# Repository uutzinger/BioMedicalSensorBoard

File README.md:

# MediBrick

A cost-effective Solution for Biomedical Measurements.

Urs Utzinger, 10/2024 and capstone teams: 24052 (2023/24), 23094 (2022/23).
Biomedical Engineering Department, The University of Arizona.

Table of Content:
<!-- TOC start (generated with https://github.com/derlin/bitdowntoc) -->

- [MediBrick](#medibrick)
   * [Problem Description](#problem-description)
   * [Project Goals](#project-goals)
   * [Measurement Solutions](#measurement-solutions)
   * [Microcontroller and Software](#microcontroller-and-software)
   * [Hardware](#hardware)
      + [Design and Manufacturing ](#design-and-manufacturing)
      + [Enclosures](#enclosures)
   * [Project Status](#project-status)

<!-- TOC end -->

<!-- TOC -->

Posters and Papers: 
- *Open source platform to measure physiological signals in a classroom setting*, BMES 2024 Annual Meeting: Biomedical Engineering Education - Poster Session C, Poster Q15 

## Problem Description

Biomedical engineering students need to practice measuring signals from living systems.
Measurement equipment is needed for classroom laboratories that can safely record common physiological parameters.
For a wide adoption, such equipment should be cost effective and repairable in-house.
Therefore, it should take advantage of existing components that are open source and distributed through domestic channels.
While there are commercial systems available [^fn1] [^fn2], there is no unifying approach that takes advantage of existing third party hardware, gives option to expand functionality at later time and uses open source software.  Such measurement modules could also be readily incorporated into academic research projects.

[^fn1]: Bioradio, https://staging.glneurotech.com/product-category/bioradio-all
[^fn2]: Protocentral https://protocentral.com

**An expandable, low-costs, open-design system is needed that measures physiological parameters in a class room setting in a safe manner.**

## Project Goals
- We strive to create an educational system to measure physiological signals.
- It shall be easily manufactured at an educational institution.
- It shall record, display and store common physiological measurements safely in a class room setting.

## Measurement Solutions
This project consists of the following measurement solutions:

| ECG and Impedance | Electronic Stethoscope and Blood Pressure | Pulse Oximeter | Temperature | Inertial Measurement Unit | Air Quality | Lung Capacity |
| --- | --- | --- | --- | --- | --- | --- |
|  |  |  |  |  |  | N.A. |
|  |  |  |  |  |  | N.A. |

Below are the relevant project files. 

Education Content: &#128214;, Sources used to find a solution: &#10004;, Solution: &#128194;, Assembly Instructions: &#128736;, Software: &#128200;

- **General Physiology Background**
    - [Cardiac Physiology](cardiac_physiology.md) &#128214;
    - [Common Physiologic Measurements](physiologic_measurements.md) &#128214;
- **Electro Cardiogram Solutions**
    - [ECG Measurement](ecg_measurements.md) &#128214;
    - [ECG Solutions](ecg_solutions.md) &#10004;
    - [ECG MediBrick v1](ECG_Board/README.md)
    - [ECG MediBrick v2](Impedance_Potential_Board/README.md) based on MAX30001G &#128194;
        - [Assembly Instructions](Impedance_Potential_Board/assembly.md) &#128736;
- **Bio Impedance Solutions**
    - [Impedance Measurement](impedance_measurements.md) &#128214;
    - [Impedance Solutions](impedance_solutions.md) &#10004;
    - [Impedance MediBrick v1](Impedance_Board/README.md) based on AD5933
    - [Impedance MediBrick v2](Impedance_Potential_Board/README.md) based on MAX30001G &#128194;
        - [Assembly Instructions](Impedance_Potential_Board/assembly.md) &#128736;
- **Stethoscope and Sound**
    - [Sound Measurement](sound_measurement.md)&#128214;
    - [Pressure Measurement](pressure_measurements.md) &#128214;
    - [Sound Solutions](sound_solutions.md) Sound Recording Solutions &#10004;
    - [Pressure Solutions](pressure_solutions.md) Pressure Recording Solutions &#10004;
    - [Stethoscope MediBrick V1](Stethoscope_with_3rdparty_Sound/README.md) PCB Artist I2S codec interfacing with ESP
    - [Stethoscope with Blood Pressure MediBrick V2](Stethoscope_with_Pressure/README.md) &#128194;
        - [Assembly Instructions](Stethoscope_with_Pressure/assembly.md) &#128736;
- **Pulse Oximeter**
    - [SpO<sub>2</sub> Measurement](spo2_measurements.md) &#128214;
    - [SpO<sub>2</sub> Solutions](spo2_solutions.md) &#10004;
    - [SpO<sub>2</sub> MediBrick](SPO2_Board/README.md) &#128194;
        - [Assembly Instructions](SPO2_Board/assembly.md) &#128736;
- **Temperature and Strain Gauges**
    - [Temperature Measurement](temperature_measurements.md) &#128214;
    - [Temperature Solutions](temperature_solutions.md) &#10004;
    - [Temperature MediBrick](Thermistor_Board/README.md) &#128194;
        - [Assembly Instructions](Thermistor_Board/assembly.md) &#128736;
- **Acceleration, Gyration, Compass and Pressure Solution**
    - [Activity Measurements with Inertial Measurement Unit](imu_measurements.md)&#128214;
    - [Inertial Measurement Unit Solutions](imu_solutions.md) &#10004;
    - [IMU MediBrick](IMU_Board/README.md)&#128194;
        - [Assembly Instructions](IMU_Board/assembly.md) &#128736;
    - IMU MediBrick v2. Not available yet, but should include Real Time Kinematic GPS such as [ZED-F9P](https://www.u-blox.com/en/product/zed-f9p-module)
- **Air Quality**
    - [Airquality Measurement](airquality_measurements.md)&#128214;
    - [Airquality Solutions](airquality_solutions.md) &#10004;
    - [Airquality MediBrick](Airquality/README.md) &#128194;
        - [Assembly Instructions](Airquality/assembly.md) &#128736;
- **Lung Capacity**
    - Not available yet, will be based on Sensirion [SFM3304-D](https://sensirion.com/products/catalog/SFM3304-D)

## Microcontroller and Software

- [Software and Programming](microcontroller_programming.md) 
- [Microcontroller Options](microcontroller_solutions.md)

To visualize data I recommend [SerialUI](https://github.com/uutzinger/SerialUI) &#128200;

## Hardware

### Design and Manufacturing 

- [Mechanical Parts Manufacturing](mechanical_design_and_manufacturing.md): Approach to convert the mechanical models to 3D printing instructions.
- [PCB Design](electronic_design.md): Settings for Eagle CAD.
- [PCB Manufacturing](pcb_manufacturing.md): Settings for PCBWay.

### Enclosures
| Assembly| Top | Bottom |
| ------- | ------ |  ------ |
|  |  |  |

Receiver

Charging Station

## Project Status

| Brick | Mechanical CAD | Electrical CAD|  Assembled | Test Software | Production Software
| ------- | ------ |  ------ | ------ | ------ | ------ |
| **Temperature**     | Completed | Completed | Completed | Completed | Working on |
| **SpO<sub>2</sub>** | Completed | Completed | Completed | Completed| Working on
| **Stethoscope**     | Completed | Testing   | Testing   | Sound Optimizing, Pressure Testing | Working on
| **Air Quality**     | Completed | Completed| Completed | MICS sensor support missing | Working on
| **IMU**             | Completed | Completed | Completed | Completed | Working on
| **Bio Potential and BIOZ** | Completed | Untested | Untested | Driver incomplete | Working on
| Protoype Sound w third arty ES8388 | Completed | Completed | Completed | Completed | N.A. |  
| Impedance w AD 5933 network analyzer | Completed | Optimization | Testing| Incomplete | N.A.|
| ECG w Sparkfun Breakout | Completed | Completed | Completed | Completed | N.A. |
| Thermistor/Strain Gauge board using LTC2473 | Completed | Completed | Completed | Completed | N.A. |

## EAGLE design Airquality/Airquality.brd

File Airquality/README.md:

# Airquality

The airquality solution uses several sensors:

| Measurand | Sensors | Manufacturer | approx. Cost |
|---        |---      | ---          | ---  |
| Particulate Matter | Sensirion | [SEN50](datasheets/Sensirion_Datasheet_Environmental_Node_SEN5x.pdf) |  $22.20 |
| CO<sub>2</sub>               | Sensirion | [SCD40](datasheets/SCD4x_Ver1.4_Feb2023.pdf)| $29.70 |
| relative Humidity and Temperature |  Sensirion | [SHT45](datasheets/Datasheet_SHT4x_1.pdf) | $6.40|
| barometric Pressure | Bosch | [BMP581](datasheets\bst_bmp581_ds004-2950309.pdf)| $4.20 |
| eVOC, eNOX | Sensirion | [SGP41](datasheets\Sensirion_Gas_Sensors_Datasheet_SGP41.pdf) | $9 |
| Carbon Monoxide, Amonia, Nitrogenoxide | Amphenol SGX Sensortech | [MiCS-6814 MEMS]((datasheets\1143_Datasheet-MiCS-6814-rev-8,pdf)) | $17 |
| Status Lights | XING Light | [Neopixel](datasheets\2301111010_XINGLIGHT-XL-2020RGBC-WS2812B_C5349955.pdf)| |

The MiCS sensor does not have an integrated analog to digital conversion and the device is measured with a resistor network. The datasheet shows operation at 5V. In this [document](MICS6814_on_3V.md) the calculations and illustration for the MiSC operating at 3V is explained. The nominal resistor values vary greatly and the detector needs tuning.

## Costs &#36;

| Item        | Quantity at Purchase | Costs  | Source            | Cost per Brick
|---                          | ---  | ---    | ---               | ---
| Microcontroller             |  1   | $17.5  | [Adafruit](https://www.adafruit.com/product/5477)          | $17.5
| Display                     |  5   | $13    | [Amazon](https://a.co/d/1QH0Ab9)            | $3
| Button                      | 25   | $9     | [Amazon](https://a.co/d/8KAuTwC) | $0.5 
| Battery                     |  1   | $10     | [Adafruit](https://www.adafruit.com/product/258)        | $10
| PCB                         |  5   | $45.20  | PCBWay            | $9
| Parts and Assembly          |  2   | $216.96 | PCBWay            | $109
| SEN50                       |  1   | $22.20  | [Mouser](https://www.mouser.com/ProductDetail/Sensirion/SEN50-SDN-T?qs=MyNHzdoqoQK%2F9NY8sYsxtw%3D%3D) | $22.20
| QWIIC cable                 |  1   | $1     | [Adafruit](https://www.adafruit.com/product/4210) | $1 |
| SEN5x cable                 | 1    | $1.50  | [Sparkfun](https://www.sparkfun.com/products/18079) | $1.50 
| Assorted Wires              |8m    | $15    | [Amazon](https://a.co/d/58djefc) | $1
| Assorted Screws and Nuts    |100   |  $7    | Amazon            | $0.05
| Assorted 3D printed parts   |      |        |                   | $3
|                             |      |        |                   |
| **Total**                   |      |        |                   | **$180**

*Electronic components excluding SEN50 are $128 per board. 

The airquality solution has been optimized for accuracy and not cost. There are sensor options for half or third of the price but they require a different board design.

## Test Software &#128187;
Test software is located in the Arduino folder.

| Folder | Description | 
|--- |---|
| MediBrick_Env_CO2_SCD4x           | CO2 sensor test             |
| MediBrick_Env_Humidity_SHT_Test   | Humidity and Temperature test |
| MediBrick_Env_PM_SEN5x_Test       | Particulate Matter test     |
| MediBrick_Env_VOC_NOx_SGP41_Test  | eVOC and NOx test           |
| MediBrick_Env_NeoPixel_Test       | RGB LED indicator test      |
| Not yet available                 | MiCS CO, Amonia Sensor, NOx test | 
## Microcontroller Software : &#9000;
An integrative software reading all sensors is not finalized yet.

## Electronics Design &#128268;

The particulate matter sensor is placed in the middle of the PCB and should not touch the PCB to avoid vibrations on the CO<sub>2</sub> sensor.

The following files are needed for PCB manufacturing and assembly.

- [Bill of Materials](Air_Quality_BOM.xlsx)
- [Manufacturing Files](Air_Quality_2024-08-24.zip)
- [Pick and Place](Air_Quality_PnP.xlsx)

The Bill of Materials is formatted so that its compatible with PCBWay submissions.

## 3D Printed Parts &#9881;
These are the links to the OnShape Design files, which you can edit and modify if you have an OnShape account (OnShape has free academic accounts).

- Medi Brick
  - [Brick Top](https://cad.onshape.com/documents/be6b7e5f847d89f3ec5eb9d5/w/761fee9865ca7ef709028476/e/ff897b4f359cec83b782ff14)
  - [Brick Bottom](https://cad.onshape.com/documents/92ad78475e8f0b17ff5e260b/w/88a02abbcb12cdbd4d9de3ad/e/fb79ca58ad2b6a0298e9d1b6)
  - [Brick Assembly](https://cad.onshape.com/documents/11cbfe9c3c739b6e8ecbf3d7/w/989b564ecd7f6d069e643ac0/e/85542f706be8cc7554218e8d)
  - [Air Quality Brick Side Plate](https://cad.onshape.com/documents/6f9a87cae125641fc3a0651c/w/6e25f32c6ac446efd4e51be7/e/7a2fa3c5e053c8442ada89bd)

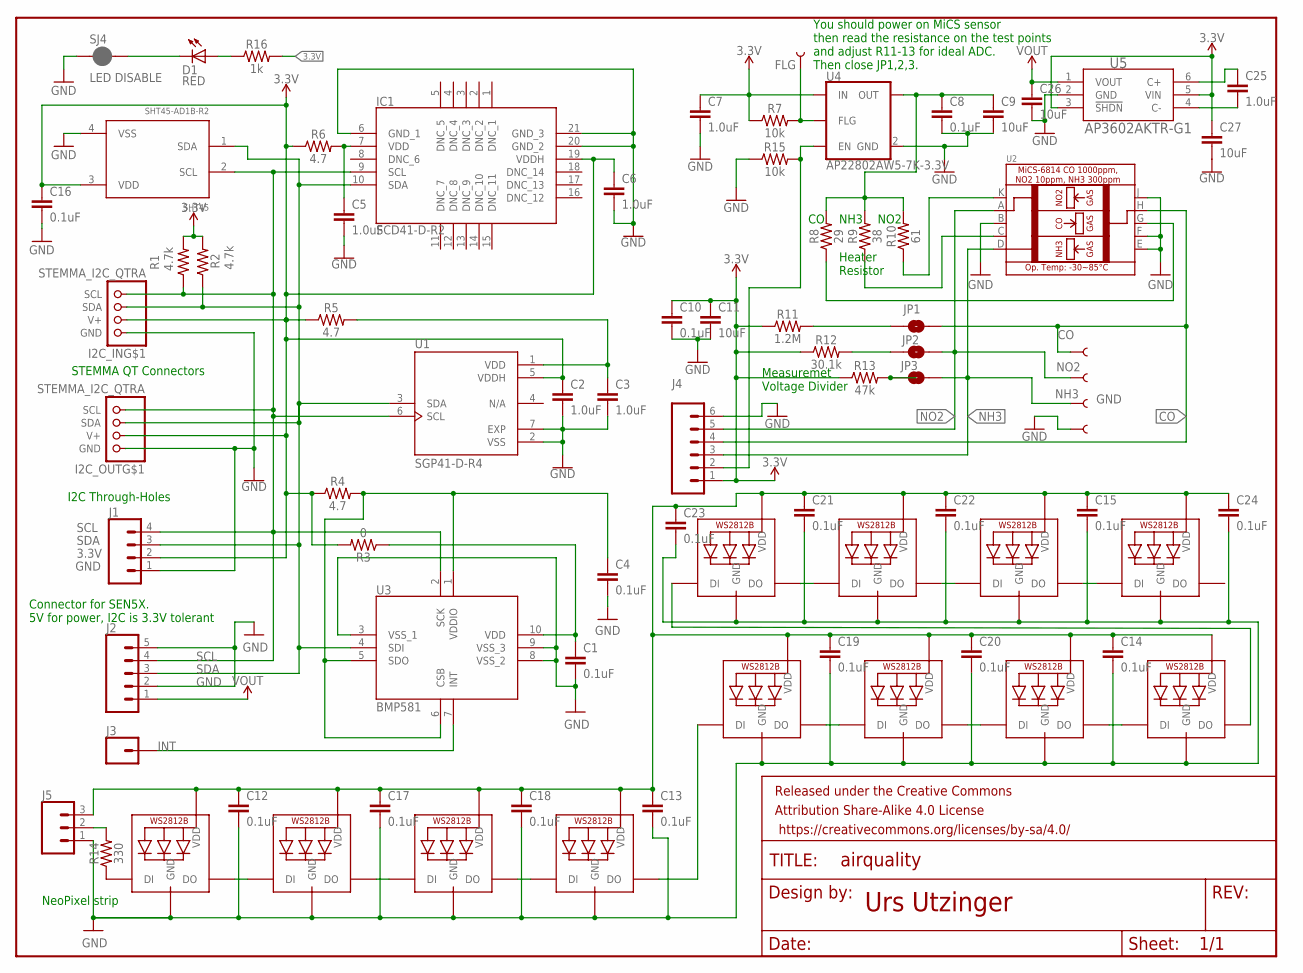
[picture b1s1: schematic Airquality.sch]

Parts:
C1, C4, C8, C10, C16: 0.1uF; 0603
C2, C3, C5, C6, C7: 1.0uF; 0603
C9, C11, C26, C27: 10uF; 0603
C12, C13, C14, C15, C17, C18, C19, C20, C21, C22, C23, C24: 0.1uF; 0402
C25: 1.0uF; 0402
CO: TEST-POINT3X4; PAD.03X.04
D1: RED; LED-0603
FLG: TEST-POINT3X4; PAD.03X.04
FRAME1: FRAME-LETTERNO_PACKAGE; DUMMY
GND: TEST-POINT3X4; PAD.03X.04
I2C_IN, I2C_OUT: STEMMA_I2C_QTRA; JST_SH4_RA
IC1: SCD41-D-R2; SCD41DR2
J1: CONN_04; 1X04
J2: CONN_05; 1X05
J3: CONN_01; 1X01
J4: CONN_06SILK_FEMALE_PTH; 1X06
J5: CONN_03; 1X03
JP1, JP2, JP3: JUMPER-SMT_2_NO_SILK; SMT-JUMPER_2_NO_SILK
LED0, LED1, LED2, LED3, LED4, LED5, LED6, LED7, LED8, LED9, LED10, LED11: WS2812B_2020
NH3: TEST-POINT3X4; PAD.03X.04
NO2: TEST-POINT3X4; PAD.03X.04
R1, R2: 4.7k; 0603
R3: 0; 0603
R4, R5, R6: 4.7; 0603
R7, R15: 10k; 0603
R8: 29; 0603
R9: 38; 0603
R10: 61; 0603
R11: 1.2M; 0603
R12: 30.1k; 0603
R13: 47k; 0603
R14: 330; 0603
R16: 1k; 0603
SHT45: SHT45-AD1B-R2; SHT4X
SJ4: LED DISABLE; SMT-JUMPER_2_NC_PASTE_SILK
U1: SGP41-D-R4; XDCR_SGP41-D-R4
U2: MICROBUILDER_MICS-5524
U3: BMP581
U4: AP22802AW5-7K-3.3V; SOT25
U5: AP3602AKTR-G1; SOT95P280X125-6N

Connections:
3.3V: C2.1, C6.1, C7.1, C10.1, C11.1, C16.1, C27.1, I2C_IN.2 (V+), I2C_OUT.2 (V+), IC1.19 (VDDH), J1.2, J4.1, R1.2, R2.2, R3.2, R4.1, R5.1, R6.1, R7.1, R11.1, R12.1, R13.1, R16.2, SHT45.3 (VDD), U1.5 (VDDH), U4.5 (IN), U5.3 (!SHDN), U5.5 (VIN)
CO: CO.P$1, J4.4, JP1.2, U2.H
GND: C1.2, C2.2, C3.2, C4.2, C5.2, C6.2, C7.2, C8.2, C9.2, C10.2, C11.2, C12.2, C13.2, C14.2, C15.2, C16.2, C17.2, C18.2, C19.2, C20.2, C21.2, C22.2, C23.2, C24.2, C26.2, C27.2, GND.P$1, I2C_IN.1 (GND), I2C_OUT.1 (GND), IC1.6 (GND_1), IC1.20 (GND_2), IC1.21 (GND_3), J1.1, J2.2, J2.5, J4.6, J5.1, LED0.2 (GND), LED1.2 (GND), LED2.2 (GND), LED3.2 (GND), LED4.2 (GND), LED5.2 (GND), LED6.2 (GND), LED7.2 (GND), LED8.2 (GND), LED9.2 (GND), LED10.2 (GND), LED11.2 (GND), R15.1, SHT45.4 (VSS), SJ4.1, U1.2 (VSS), U1.7 (EXP), U2.B, U2.E, U2.F, U2.J, U3.3 (VSS_1), U3.8 (VSS_2), U3.9 (VSS_3), U4.2 (GND), U5.2 (GND)
INT: J3.1, U3.7 (INT)
unnamed: C4.1, R4.2, U3.1 (VDDIO), U3.5 (SDO), U3.6 (CSB)
unnamed: C1.1, R3.1, U3.10 (VDD)
unnamed: FLG.P$1, R7.2, U4.3 (FLG)
unnamed: C3.1, R5.2, U1.1 (VDD)
unnamed: C5.1, IC1.7 (VDD), R6.2
unnamed: LED0.1 (DO), LED1.3 (DI)
unnamed: C8.1, C9.1, R8.2, R9.2, R10.2, U4.1 (OUT)
unnamed: R10.1, U2.K
unnamed: JP1.1, R11.2
unnamed: R9.1, U2.C
unnamed: JP2.1, R12.2
unnamed: R8.1, U2.G
unnamed: JP3.1, R13.2
unnamed: C25.1, U5.6 (C+)
unnamed: LED1.1 (DO), LED2.3 (DI)
unnamed: LED2.1 (DO), LED3.3 (DI)
unnamed: LED4.1 (DO), LED5.3 (DI)
unnamed: LED5.1 (DO), LED6.3 (DI)
unnamed: LED6.1 (DO), LED7.3 (DI)
unnamed: LED3.1 (DO), LED4.3 (DI)
unnamed: J5.2, R14.2
unnamed: LED0.3 (DI), R14.1
unnamed: LED7.1 (DO), LED8.3 (DI)
unnamed: LED10.1 (DO), LED11.3 (DI)
unnamed: D1.A, R16.1
unnamed: LED9.1 (DO), LED10.3 (DI)
unnamed: D1.C, SJ4.2
unnamed: LED8.1 (DO), LED9.3 (DI)
unnamed: C25.2, U5.4 (C-)
unnamed: C12.1, C13.1, C14.1, C15.1, C17.1, C18.1, C19.1, C20.1, C21.1, C22.1, C23.1, C24.1, J5.3, LED0.4 (VDD), LED1.4 (VDD), LED2.4 (VDD), LED3.4 (VDD), LED4.4 (VDD), LED5.4 (VDD), LED6.4 (VDD), LED7.4 (VDD), LED8.4 (VDD), LED9.4 (VDD), LED10.4 (VDD), LED11.4 (VDD)
unnamed: J4.2, R15.2, U4.4 (EN)
NH3: J4.3, JP3.2, NH3.P$1, U2.D
NO2: J4.5, JP2.2, NO2.P$1, U2.A
SCL: I2C_IN.4 (SCL), I2C_OUT.4 (SCL), IC1.9 (SCL), J1.4, J2.4, R1.1, SHT45.2 (SCL), U1.6 (SCL), U3.2 (SCK)
SDA: I2C_IN.3 (SDA), I2C_OUT.3 (SDA), IC1.10 (SDA), J1.3, J2.3, R2.1, SHT45.1 (SDA), U1.3 (SDA), U3.4 (SDI)
VOUT: C26.1, J2.1, U5.1 (VOUT)

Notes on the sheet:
STEMMA QT Connectors
I2C Through-Holes
Urs Utzinger
You should power on MiCS sensor then read the resistance on the test points and adjust R11-13 for ideal ADC. Then close JP1,2,3.
Connector for SEN5X. 5V for power, I2C is 3.3V tolerant
NeoPixel strip
NH3
NO2
Measuremet Voltage Divider
Heater Resistor

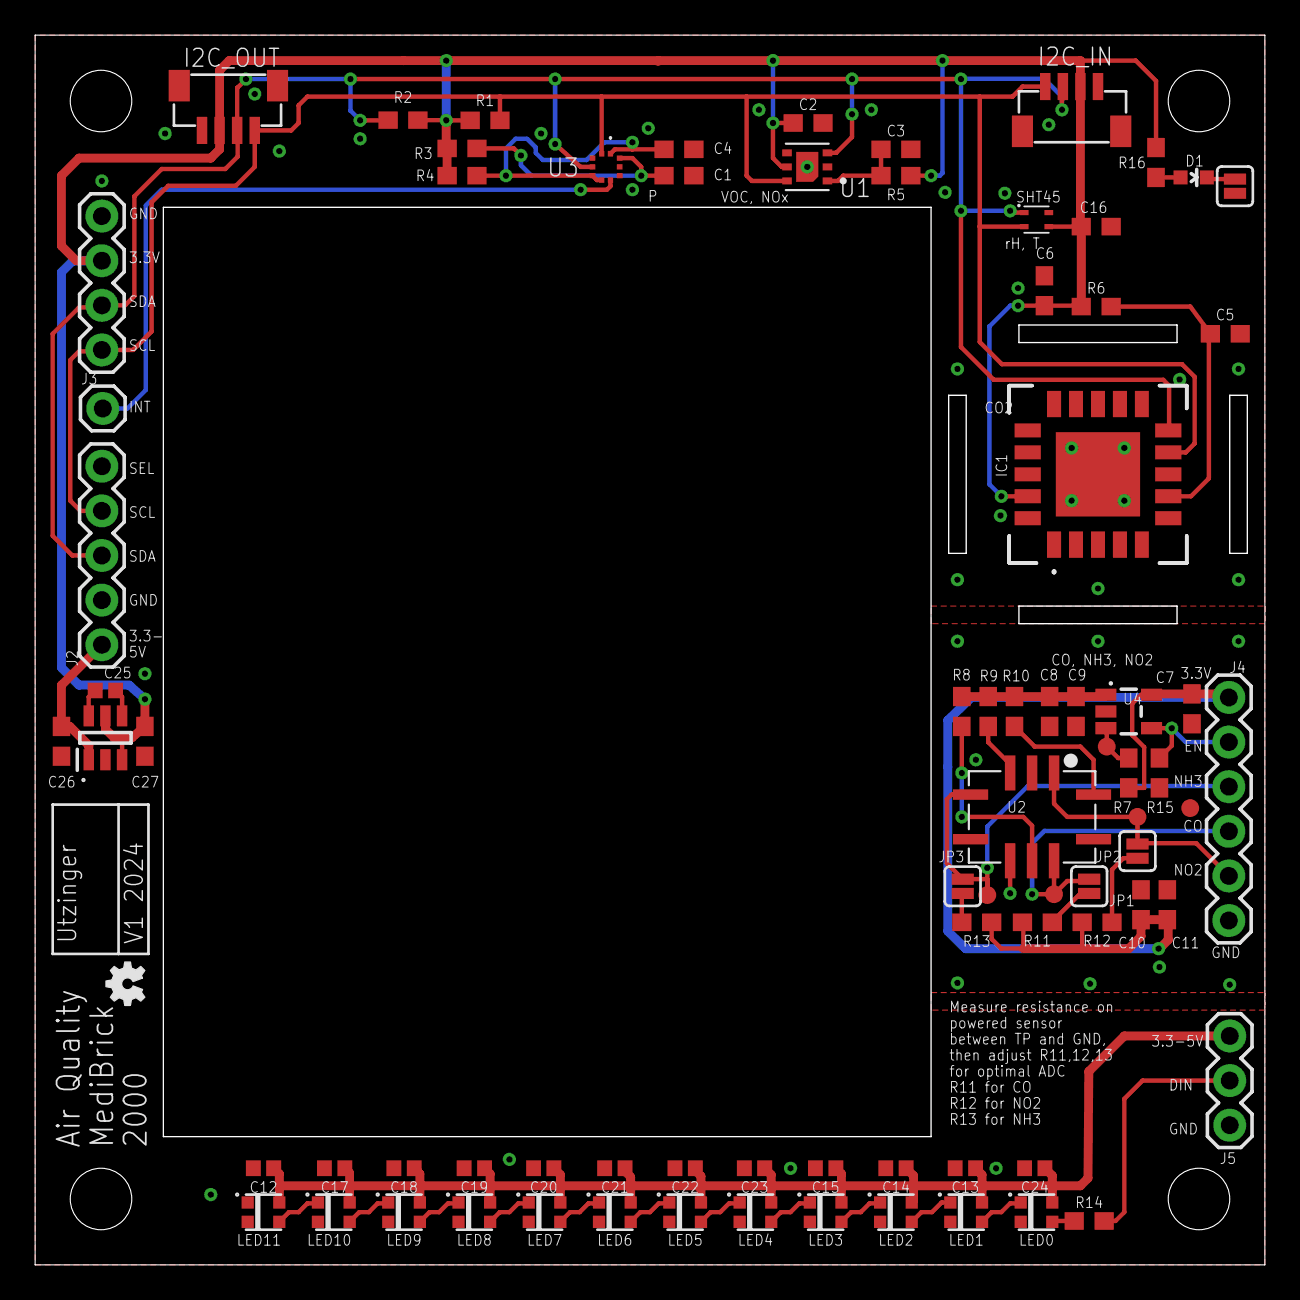
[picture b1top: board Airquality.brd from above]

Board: 2 copper layers, 70.0 x 70.0 mm, 81 parts (0 on the bottom side), 40 nets.

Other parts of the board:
U$2: OSHW-LOGO-MINI

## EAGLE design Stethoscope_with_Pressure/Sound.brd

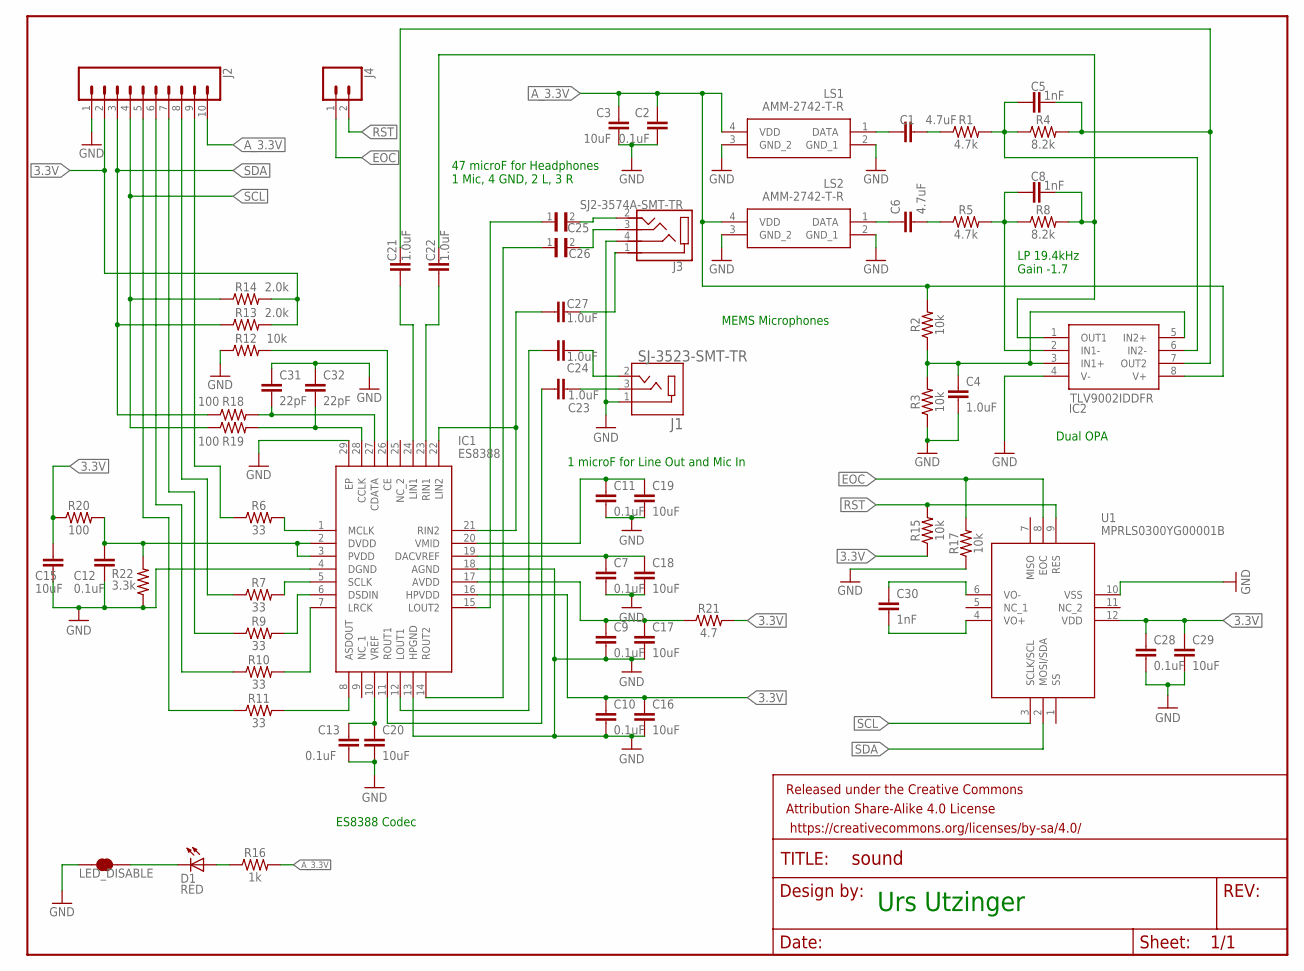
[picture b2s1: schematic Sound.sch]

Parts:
C1, C6: 4.7uF; 0603
C2, C7, C9, C10, C11, C12, C13, C28: 0.1uF; 0603
C3, C15, C16, C17, C18, C19, C20, C29: 10uF; 0603
C4, C21, C22, C23, C24, C27: 1.0uF; 0603
C5, C8, C30: 1nF; 0603
C25, C26: GRM188R60J476ME15D; CAPC1608X100N
C31, C32: 22pF; 0603
D1: RED; LED-0603
FRAME1: FRAME-LETTERNO_PACKAGE; DUMMY
IC1: ES8388; QFN45P400X400X90-29N
IC2: TLV9002IDDFR; SOT65P280X110-8N
J1: SJ-3523-SMT-TR; CUI_SJ-3523-SMT-TR
J2: CONN_10"; 1X10
J3: SJ2-3574A-SMT-TR; CUI_SJ2-3574A-SMT-TR
J4: CONN_02; 1X02
LED_DISABLE: JUMPER-SMT_2_NC_TRACE_SILK; SMT-JUMPER_2_NC_TRACE_SILK
LS1, LS2: AMM-2742-T-R; AMM2742TR
R1, R5: 4.7k; 0603
R2, R3, R12, R15, R17: 10k; 0603
R4, R8: 8.2k; 0603
R6, R7, R9, R10, R11: 33; 0603
R13, R14: 2.0k; 0603
R16: 1k; 0603
R18, R19, R20: 100; 0603
R21: 4.7; 0603
R22: 3.3k; 0603
U1: MPRLS0300YG00001B

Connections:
3.3V: C10.1, C15.1, C16.1, C28.1, C29.1, IC1.16 (HPVDD), J2.2, R13.2, R14.2, R15.1, R20.1, R21.2, U1.12 (VDD)
A_3.3V: C2.1, C3.1, IC2.8 (V+), J2.10, LS1.4 (VDD), LS2.4 (VDD), R2.2, R16.2
DIN: J2.7, R9.1
DOUT: J2.5, R11.1
EOC: J4.1, R17.2, U1.8 (EOC)
GND: C2.2, C3.2, C4.2, C7.2, C9.2, C10.2, C11.2, C12.2, C13.2, C15.2, C16.2, C17.2, C18.2, C19.2, C20.2, C28.2, C29.2, C31.1, C32.1, IC1.4 (DGND), IC1.13 (HPGND), IC1.18 (AGND), IC1.29 (EP), IC2.4 (V-), J1.1, J2.1, J3.4, LED_DISABLE.1, LS1.2 (GND_1), LS1.3 (GND_2), LS2.2 (GND_1), LS2.3 (GND_2), R3.1, R12.1, R17.1, R22.1, U1.10 (VSS)
LRCLK: J2.6, R10.1
MCLK: J2.9, R6.1
unnamed: IC1.26 (CE), R12.2
unnamed: C8.2, C22.2, IC2.1 (OUT1), R8.2
unnamed: C22.1, IC1.23 (RIN1)
unnamed: C21.1, IC1.24 (LIN1)
unnamed: C31.2, IC1.27 (CDATA), R18.2
unnamed: C32.2, IC1.28 (CCLK), R19.2
unnamed: C11.1, C19.1, IC1.20 (VMID)
unnamed: C30.1, U1.6 (VO-)
unnamed: C5.2, C21.2, IC2.7 (OUT2), R4.2
unnamed: C30.2, U1.4 (VO+)
unnamed: C1.1, LS1.1 (DATA)
unnamed: C9.1, C17.1, IC1.17 (AVDD), R21.1
unnamed: C1.2, R1.1
unnamed: C5.1, IC2.6 (IN2-), R1.2, R4.1
unnamed: C4.1, IC2.3 (IN1+), IC2.5 (IN2+), R2.1, R3.2
unnamed: C12.1, IC1.2 (DVDD), IC1.3 (PVDD), R20.2, R22.2
unnamed: C6.1, LS2.1 (DATA)
unnamed: C6.2, R5.1
unnamed: C8.1, IC2.2 (IN1-), R5.2, R8.1
unnamed: IC1.8 (ASDOUT), R11.2
unnamed: IC1.7 (LRCK), R10.2
unnamed: C13.1, C20.1, IC1.10 (VREF)
unnamed: IC1.6 (DSDIN), R9.2
unnamed: IC1.5 (SCLK), R7.2
unnamed: D1.A, R16.1
unnamed: IC1.1 (MCLK), R6.2
unnamed: D1.C, LED_DISABLE.2
unnamed: C23.2, IC1.11 (ROUT1)
unnamed: C24.1, J1.2
unnamed: C7.1, C18.1, IC1.19 (DACVREF)
unnamed: C24.2, IC1.12 (LOUT1)
unnamed: C25.2, J3.2
unnamed: C23.1, J1.3
unnamed: C26.2, J3.3
unnamed: C27.2, J3.1
unnamed: C27.1, IC1.21 (RIN2), IC1.22 (LIN2)
unnamed: C26.1, IC1.14 (ROUT2)
unnamed: C25.1, IC1.15 (LOUT2)
RST: J4.2, R15.2, U1.9 (RES)
SCL: J2.4, R14.1, R19.1, U1.3 (SCLK/SCL)
SCLK: J2.8, R7.1
SDA: J2.3, R13.1, R18.1, U1.2 (MOSI/SDA)

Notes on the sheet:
MEMS Microphones
Dual OPA
47 microF for Headphones 1 Mic, 4 GND, 2 L, 3 R
1 microF for Line Out and Mic In
Urs Utzinger
ES8388 Codec
LP 19.4kHz Gain -1.7

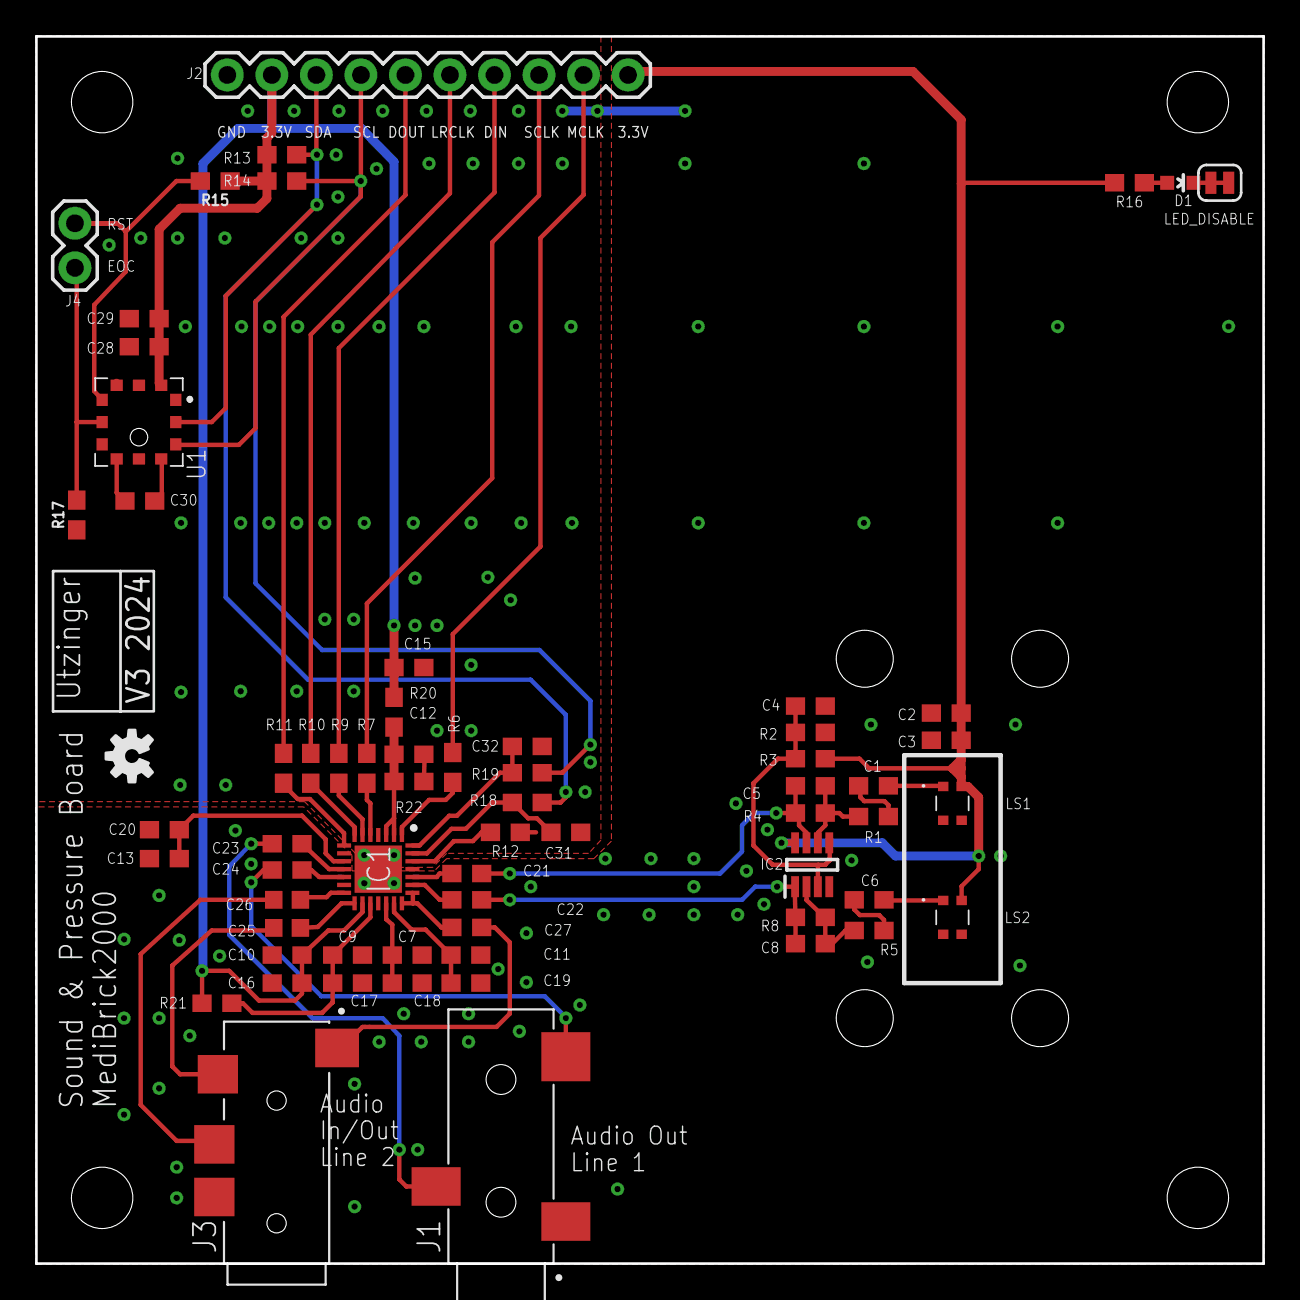
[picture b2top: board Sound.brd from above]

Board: 2 copper layers, 70.0 x 70.0 mm, 66 parts (0 on the bottom side), 50 nets.

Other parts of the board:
U$3: OSHW-LOGO-S

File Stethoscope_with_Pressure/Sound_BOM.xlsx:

Item # | Designator | Qty | Manufacturer | Mfg Part # | LCSC Part# | U.S. Distributor | Description / Value | *Package/Footprint | Mounting Type | Your Instructions / Notes
1 | C2, C7, C9, C10, C11, C12, C13, C28 | 8 | Samsung Electro-Mechanics | CL10B104KA8NNNC | C1590 |  | 0.1uF | 0603 | SMD
2 | C4, C21, C22, C23, C24, C27 | 6 | Samsung Electro-Mechanics | CL10A105KA8NNNC | C5673 |  | 1.0uF | 0603 | SMD
3 | C3, C15, C16, C17, C18, C19, C20, C29 | 8 | Samsung Electro-Mechanics | CL10A106MA8NRNC | C96446 |  | 10uF | 0603 | SMD
4 | C1, C6 | 2 | Samsung Electro-Mechanics | CL10A475KA8NQNC | C69335 |  | 4.7uF | 0603 | SMD
5 | C5, C8 | 2 | Samsung Electro-Mechanics | CL10C102JB8NNNC | C163508 |  | 1000pF | 0603 | SMD | Was 82.pF in version 2
6 | C25, C26 | 2 | Samsung Electro-Mechanics | CL10A476MQ8QRNC | C730416 |  | 47uF | 0603 | SMD
7 | C30 | 1 | Samsung Electro-Mechanics | CL10B102KB8NNNC | C1588 |  | 1nF | 0603 | SMD
8 | C31, C32 | 2 | Samsung Electro-Mechanics | CL10C220JB8NNNC | C1653 |  | 22pF | 0603 | SMD
9 | R1, R5 | 2 | YAGEO | RC0603FR-074K7L | C99782 |  | 4.7k | 0603 | SMD
10 | R2, R3, R12, R15, R17 | 5 | YAGEO | RC0603FR-0710KL | C98220 |  | 10k | 0603 | SMD
11 | R4, R8 | 2 | YAGEO | RC0603FR-078K2L | C114637 |  | 8.2k | 0603 | SMD | Was 100k in version 2
12 | R6, R7, R9, R10, R11 | 5 | YAGEO | RC0603FR-0733RL | C108661 |  | 33 | 0603 | SMD
13 | R13, R14 | 2 | YAGEO | RC0603FR-072KL | C105576 |  | 2k | 0603 | SMD
14 | R16 | 1 | YAGEO | RC0603FR-071KL | C22548 |  | 1k | 0603 | SMD
15 | R18, R19, R20 | 3 | YAGEO | RC0603FR-07100RL | C105588 |  | 100 | 0603 | SMD
16 | R21 | 1 | YAGEO | RC0603FR-074R7L | C137705 |  | 4.7 | 0603 | SMD
17 | R22 | 1 | YAGEO | RC0603FR-073K3L | C108078 |  | 3.3k | 0603 | SMD
18 | LS1, LS2 | 2 | PUI Audio, Inc. | AMM-2742-T-R | C3171735 | https://www.mouser.com/ProductDetail/PUI-Audio/AMM-2742-T-R?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 | AMM-2742-T-R, MEMS Microphones | 0603 | SMD
19 | IC1 | 1 | Everest-semi(Everest Semiconductor) | ES8388 | C365736 |  | ES8388 | QFN-28-EP(4x4) | SMD
20 | D1 | 1 | XINGLIGHT | XL-1608UBC-04 | C965807 |  | Blue LED | 0603 | SMD
21 | J1 | 1 | CUI Devices | SJ-3523-SMT-TR |  | https://www.mouser.com/ProductDetail/CUI-Devices/SJ-3523-SMT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 | SJ-3523-SMT-TR, 3.5mm Audio Jack |  | SMD
22 | J3 | 1 | CUI Devices | SJ2-3574A-SMT-TR |  | https://www.mouser.com/ProductDetail/CUI-Devices/SJ2-3574A-S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 | SJ2-3574A-SMT-TR, 3.5mm Audio Jack with microphone |  | SMD
23 | IC2 | 1 | Texas Instruments | TLV9002IDDFR | C2862620 |  | TLV9002IDDFR, Dual OpAmp | TSOT-23-8 | SMD
 |  | 60
 | Resistors | 22
 | Capacitors | 31

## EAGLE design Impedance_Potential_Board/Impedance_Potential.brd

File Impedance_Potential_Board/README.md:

# Bio Impedance and Bio Potential

In the BIOZ and ECG MediBrick we use the MAXIM [MAX30001G](datasheets/max30001g.pdf) analog front end (AFE). It's a modern IC with a "waver level packaging" foot print which makes is difficult to solder and requires precise PCB manufacturing.

The MAX30001G can measure:

- Biopotential
  - ECG (waveform)
  - R-R Time (heart rate and heart rate variability)
- Bioimpedance
  - Resp (respiration rate)
  - GSR (galvanic skin response, stress level)
  - EDA (electro dermal activity)

Here [MAX3001G](MAX30001G.md) we summary capabilities from the datasheet.

For general consideration of bio impedance design and safety: [Analog Devices: Bio-Impedance Circuit Design for Body Worn Systems"](https://www.analog.com/en/resources/analog-dialogue/articles/bioimpedance-circuit-design-challenges.html)

## Costs &#36;

| Item        | Quantity at Purchase | Costs  | Source            | Cost per Brick
|---                          | ---  | ---    | ---               | ---
| Microcontroller             |  1   | $17.5  | [Adafruit](https://www.adafruit.com/product/5477)          | $17.5
| Display                     |  5   | $13    | [Amazon](https://a.co/d/1QH0Ab9)            | $3
| Button                      | 25   | $9     | [Amazon](https://a.co/d/8KAuTwC) | $0.5 
| Battery                     |  1   | $10     | [Adafruit](https://www.adafruit.com/product/258)        | $10
| PCB                         |  5   | $145.80 | PCBWay            | $29
| Parts and Assembly          |  5   | $186.42 | PCBWay            | $38
| Assorted Wires              |8m    | $15    | [Amazon](https://a.co/d/58djefc) | $1
| Assorted Screws and Nuts    |100   |  $7    | Amazon            | $0.05
| Assorted 3D printed parts   |      |        |                   | $3
| ECG 3.5mm cables | 1  | $5.50 | [Sparkfun](https://www.sparkfun.com/products/12970) | $5.50
| Electrodes (consumable) | 100 | $25 | [Amazon](https://a.co/d/85M2rC2) | $ 1
|                             |      |        |                   |
| **Total**                   |      |        |                   | **$110**

Electronic components are $20 per board. Because of WLP foot print of MAX30001G the PCB is 3 times as expensive as the other PCBs.

## Test Software &#128187;
Test software is located in the Arduino folder.

| Folder | Description | 
|--- |---|
| MAX30001G Driver | under development |
| Test programs    | not available yet |

## Microcontroller Software : &#9000;
Not available yet.

## Electronics Design &#128268;

The following files are needed for PCB manufacturing and assembly.

- [Bill of Materials](Impedance_Potential_BOM.xlsx)
- [Manufacturing Files](Impedance_Potential_2024-09-12.zip)
- [Pick and Place](Impedance_Potential_PnP.xlsx)

The Bill of Materials is formatted so that its compatible with PCBWay submissions.

## 3D Printed Parts &#9881;
These are the links to the OnShape Design files, which you can edit and modify if you have an OnShape account (OnShape has free academic accounts).

- Medi Brick
  - [Brick Top](https://cad.onshape.com/documents/be6b7e5f847d89f3ec5eb9d5/w/761fee9865ca7ef709028476/e/ff897b4f359cec83b782ff14)
  - [Brick Bottom](https://cad.onshape.com/documents/92ad78475e8f0b17ff5e260b/w/88a02abbcb12cdbd4d9de3ad/e/fb79ca58ad2b6a0298e9d1b6)
  - [Brick Assembly](https://cad.onshape.com/documents/11cbfe9c3c739b6e8ecbf3d7/w/989b564ecd7f6d069e643ac0/e/85542f706be8cc7554218e8d)
  - [Impedance Potential Plate](https://cad.onshape.com/documents/4b23bdc1fe41aa5490b46d9c/w/fd4737f6a1ca7fbcd3b1d7f7/e/89122d5ddac798ebf451ad60)

## MAX30001G Design

## Block Diagram of MAX 30001G

## External Configuration Options

We have the following external connectors:
- ECG, 3,5mm audio
    - ECG_N (middle of plug) e.g. left arm
    - ECG_P (proximal side of plug) e.g. right arm
    - VCM/ECG_GND (common mode) (tip of plug) e.g. leg

- Impedance, 3.5mm audio
    - BI_N
    - BI_P
    - GND (tip of plug)

- Driver, 3.5mm audio
    - DRV_P
    - DRV_N
    - GND (tip of plug)

### Options
- We can operate the board to measure ECG or Impedance or both. 
- We can operate the board to use only two leads, four leads or six leads. 
    - 6 leads ECG on ECGP & ECGN, BIOZ on BINP & BINN and DRV on DRVP & DRVN
    - 4 leads ECG on ECGP & ECGN, BIOZ on BINP & BINN
    - 2 leads ECG, BIOZ, DRV on ECGP & ECGN
- We can configure the board to measure impedance of a calibration resistor that is soldered onto the board (100 Ohm).

### Component Values

Typical values and conditions of external components

Name      | typical value | Comment
----------|---------------|--------
C_ECG     | 2.2nF         | datasheet
C_ECG-G   | 10pF          | datasheet, 47pF protocentral
EP_EN     | open          | if closed disable ECG
R_ECG     | 0,51k,200k Ohm | 0, 200k shown in datasheet (200k when ECG conencted with BIOZ), 51k protocentral, 0 Ohm evaluation kit
R_ECG-B   | 51k           | evaluation kit
C_ECG_B   | 47nF          | evaluation kit
ECG_UNBAL | open          | if closed disable balancing
||
EP_BP     | open          | impedance and ECG is on different plug
EN_BN     | open          | impedance and ECG is on different plug
||
C_BIN     | 47pF          | datasheet
C_BIN_G   | 10pF          | datasheet
BP_BN     | open          | if closed disable BioZ
R_BIN     | 0, 200 Ohm    | 200 protocentral where ECG is connected to BIN, 0 evaluation kit
R_CAL     | 100 Ohm       | evaluation kit
RP        | open          | if closed no external impedance
RN        | open          | "
||
BP_DP     | open          | impedance and driver on different plug
BN_DN     | open          | impedance and driver on different plug
||
C_DRV     | 200nF, 47nF   | 47nF protocentral, 47nF evaluation kit
||
R_VCM     | 0 Ohm,10k,200k| 10k protocentral, evaluation kit has buffer driver circuit, 200k datasheet
R_VCM-B   | 51k, none     | none protocentral & evaluation kit
C_VCM-B   | 47nF, none    | none protocentral & evaluation kit, 47nF datasheet
VMC_UNBAL | open          |

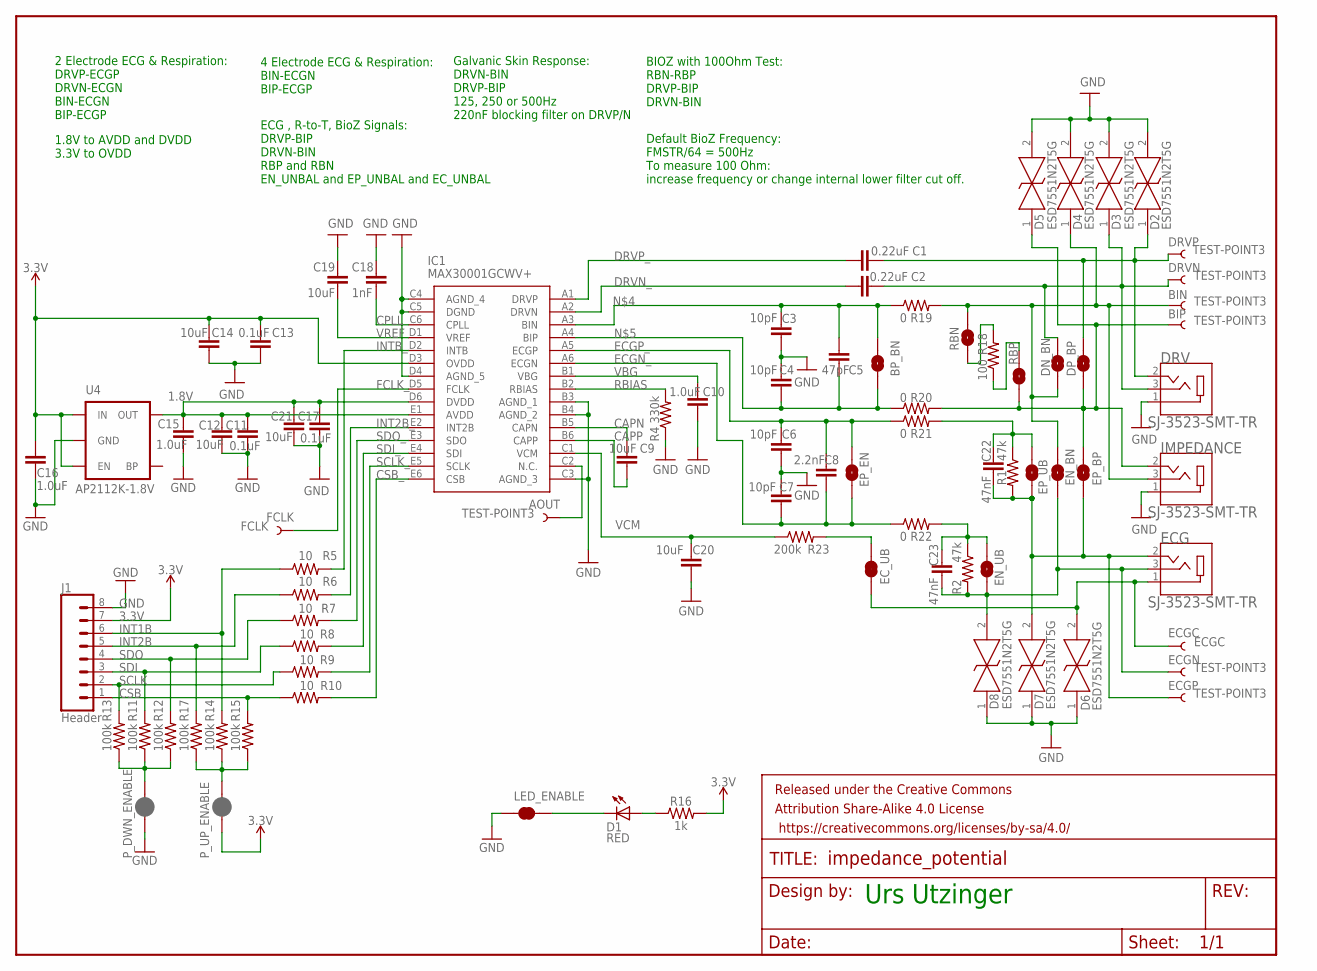
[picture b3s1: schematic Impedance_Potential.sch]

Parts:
AOUT: TEST-POINT3; PAD.03X.03
BIN: TEST-POINT3; PAD.03X.03
BIP: TEST-POINT3; PAD.03X.03
BP_BN: JUMPER-SMT_2_NO_SILK; SMT-JUMPER_2_NO_SILK
C1, C2: 0.22uF; 0603
C3, C4, C6, C7: 10pF; 0603
C5: 47pF; 0603
C8: 2.2nF; 0603
C9, C12, C14, C19, C20, C21: 10uF; 0603
C10, C15, C16: 1.0uF; 0603
C11, C13, C17: 0.1uF; 0603
C18: 1nF; 0603
C22, C23: 47nF; 0603
D1: RED; LED-0603
D2, D3, D4, D5, D6, D7, D8: ESD7551N2T5G
DN_BN: JUMPER-SMT_2_NO_SILK; SMT-JUMPER_2_NO_SILK
DP_BP: JUMPER-SMT_2_NO_SILK; SMT-JUMPER_2_NO_SILK
DRV: SJ-3523-SMT-TR; CUI_SJ-3523-SMT-TR
DRVN: TEST-POINT3; PAD.03X.03
DRVP: TEST-POINT3; PAD.03X.03
ECG: SJ-3523-SMT-TR; CUI_SJ-3523-SMT-TR
ECGC: ECGC; PAD.03X.03
ECGN: TEST-POINT3; PAD.03X.03
ECGP: TEST-POINT3; PAD.03X.03
EC_UB: JUMPER-SMT_2_NC_TRACE_SILK; SMT-JUMPER_2_NC_TRACE_SILK
EN_BN: JUMPER-SMT_2_NO_SILK; SMT-JUMPER_2_NO_SILK
EN_UB: JUMPER-SMT_2_NO_SILK; SMT-JUMPER_2_NO_SILK
EP_BP: JUMPER-SMT_2_NO_SILK; SMT-JUMPER_2_NO_SILK
EP_EN: JUMPER-SMT_2_NO_SILK; SMT-JUMPER_2_NO_SILK
EP_UB: JUMPER-SMT_2_NO_SILK; SMT-JUMPER_2_NO_SILK
FCLK: FCLK; PAD.03X.03
FRAME1: FRAME-LETTERNO_PACKAGE; DUMMY
IC1: MAX30001GCWV+; BGA30C50P6X5_293X274X69
IMPEDANCE: SJ-3523-SMT-TR; CUI_SJ-3523-SMT-TR
J1: Header; 1X08
LED_ENABLE: LED ENABLE; SMT-JUMPER_2_NC_TRACE_SILK
P_DWN_ENABLE: JUMPER-SMT_2_NC_PASTE_SILK; SMT-JUMPER_2_NC_PASTE_SILK
P_UP_ENABLE: JUMPER-SMT_2_NC_PASTE_SILK; SMT-JUMPER_2_NC_PASTE_SILK
R1, R2: 47k; 0603
R4: 330k; 0603
R5, R6, R7, R8, R9, R10: 10; 0603
R11, R12, R13, R14, R15, R17: 100k; 0603
R16: 1k; 0603
R18: 100; 0603
R19, R20, R21, R22: 0; 0603
R23: 200k; 0603
RBN: JUMPER-SMT_2_NO_SILK; SMT-JUMPER_2_NO_SILK
RBP: JUMPER-SMT_2_NO_SILK; SMT-JUMPER_2_NO_SILK
U4: AP2112K-1.8V; SPARKFUN-POWERIC_SOT23-5

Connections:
1.8V: C11.1, C12.1, C15.2, C17.1, C21.1, IC1.D6 (DVDD), IC1.E1 (AVDD), U4.5 (OUT)
3.3V: C13.1, C14.1, C16.2, IC1.D3 (OVDD), J1.7, P_UP_ENABLE.1, R16.2, U4.1 (IN), U4.3 (EN)
AOUT: AOUT.P$1, IC1.C2 (N.C.)
BIN: BIN.P$1, D4.1, DN_BN.1, EN_BN.2, IMPEDANCE.3, R19.2, RBN.2
BIP: BIP.P$1, D5.1, DP_BP.1, EP_BP.2, IMPEDANCE.2, R20.2, RBP.1
CAPN: C9.1, IC1.B5 (CAPN)
CAPP: C9.2, IC1.B6 (CAPP)
CPLL: C18.2, IC1.C6 (CPLL)
CSB: J1.1, R10.1, R15.2
CSB_: IC1.E6 (CSB), R10.2
DRVN: C2.2, D3.1, DN_BN.2, DRV.3, DRVN.P$1
DRVN_: C2.1, IC1.A2 (DRVN)
DRVP: C1.2, D2.1, DP_BP.2, DRV.2, DRVP.P$1
DRVP_: C1.1, IC1.A1 (DRVP)
ECGC: D6.2, ECG.1, ECGC.P$1, EC_UB.1
ECGN: C23.2, D8.2, ECG.3, ECGN.P$1, EN_BN.1, EN_UB.1, R2.2
ECGN_: C7.2, C8.2, EP_EN.1, IC1.A6 (ECGN), R22.1
ECGP: C22.2, D7.2, ECG.2, ECGP.P$1, EP_BP.1, EP_UB.1, R1.2
ECGP_: C6.1, C8.1, EP_EN.2, IC1.A5 (ECGP), R21.1
FCLK_: FCLK.P$1, IC1.D5 (FCLK)
GND: C3.2, C4.1, C6.2, C7.1, C10.2, C11.2, C12.2, C13.2, C14.2, C15.1, C16.1, C17.2, C18.1, C19.1, C20.2, C21.2, D2.2, D3.2, D4.2, D5.2, D6.1, D7.1, D8.1, DRV.1, IC1.B3 (AGND_1), IC1.B4 (AGND_2), IC1.C3 (AGND_3), IC1.C4 (AGND_4), IC1.C5 (DGND), IC1.D4 (AGND_5), IMPEDANCE.1, J1.8, LED_ENABLE.1, P_DWN_ENABLE.1, R4.1, U4.2 (GND)
INT1B: J1.6, R5.1, R14.2
INT2B: J1.5, R6.1, R17.2
INT2B_: IC1.E2 (INT2B), R6.2
INTB_: IC1.D2 (INTB), R5.2
unnamed: C23.1, EN_UB.2, R2.1, R22.2
unnamed: EC_UB.2, R23.2
unnamed: C22.1, EP_UB.2, R1.1, R21.2
unnamed: BP_BN.2, C3.1, C5.1, IC1.A3 (BIN), R19.1
unnamed: BP_BN.1, C4.2, C5.2, IC1.A4 (BIP), R20.1
unnamed: D1.A, R16.1
unnamed: D1.C, LED_ENABLE.2
unnamed: P_DWN_ENABLE.2, R11.1, R12.1, R13.1
unnamed: P_UP_ENABLE.2, R14.1, R15.1, R17.1
unnamed: R18.2, RBN.1
unnamed: R18.1, RBP.2
RBIAS: IC1.B2 (RBIAS), R4.2
SCLK: J1.2, R9.1, R13.2
SCLK_: IC1.E5 (SCLK), R9.2
SDI: J1.3, R8.1, R11.2
SDI_: IC1.E4 (SDI), R8.2
SDO: J1.4, R7.1, R12.2
SDO_: IC1.E3 (SDO), R7.2
VBG: C10.1, IC1.B1 (VBG)
VCM: C20.1, IC1.C1 (VCM), R23.1
VREF: C19.2, IC1.D1 (VREF)

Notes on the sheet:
2 Electrode ECG & Respiration: DRVP-ECGP DRVN-ECGN BIN-ECGN BIP-ECGP
4 Electrode ECG & Respiration: BIN-ECGN BIP-ECGP
Galvanic Skin Response: DRVN-BIN DRVP-BIP 125, 250 or 500Hz 220nF blocking filter on DRVP/N
BIOZ with 100Ohm Test: RBN-RBP DRVP-BIP DRVN-BIN
1.8V to AVDD and DVDD 3.3V to OVDD
ECG , R-to-T, BioZ Signals: DRVP-BIP DRVN-BIN RBP and RBN EN_UNBAL and EP_UNBAL and EC_UNBAL
Default BioZ Frequency: FMSTR/64 = 500Hz To measure 100 Ohm: increase frequency or change internal lower filter cut off.
Urs Utzinger

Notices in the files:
parts and their libraries:
SparkFun-Connectors: Licensing: Creative Commons ShareAlike 4.0 International - https://creativecommons.org/licenses/by-sa/4.0
SparkFun-LED: Licensing: CC v3.0 Share-Alike You are welcome to use this library for commercial purposes.
SparkFun-Aesthetics: Released under the Creative Commons
